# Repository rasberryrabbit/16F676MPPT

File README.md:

# PIC16F676MPPT
Solar MPPT circuit by 16F676. It did tested and work good.

This is simple MPPT for solar panel. PWM driven by software.

11 mili-ohm N-ch logic level FET(BUK9511) used for current sensor. 
It can replace by 11 mili-ohm or higher Rds-on resistance logic level FET.

BUK9511-55A -> BUK9508-55A
Transistor 2N2222A -> BC547 or compatible
Transistor 2N2907A -> BC557 or compatible

L1 100~330uH

LM358N can replace by other pin-compatible regular OP-AMP. HA17358 is good. It has zero offset voltage.

D8-D9 used for 3.6v Reference. Each has about 1.8v voltage drop.

Q1 gate voltage is 3.6v. It's depend on FET specification.

Q1, Q2 can skip heat spreader with low POWER Solar panel. No heat with 10W panel.

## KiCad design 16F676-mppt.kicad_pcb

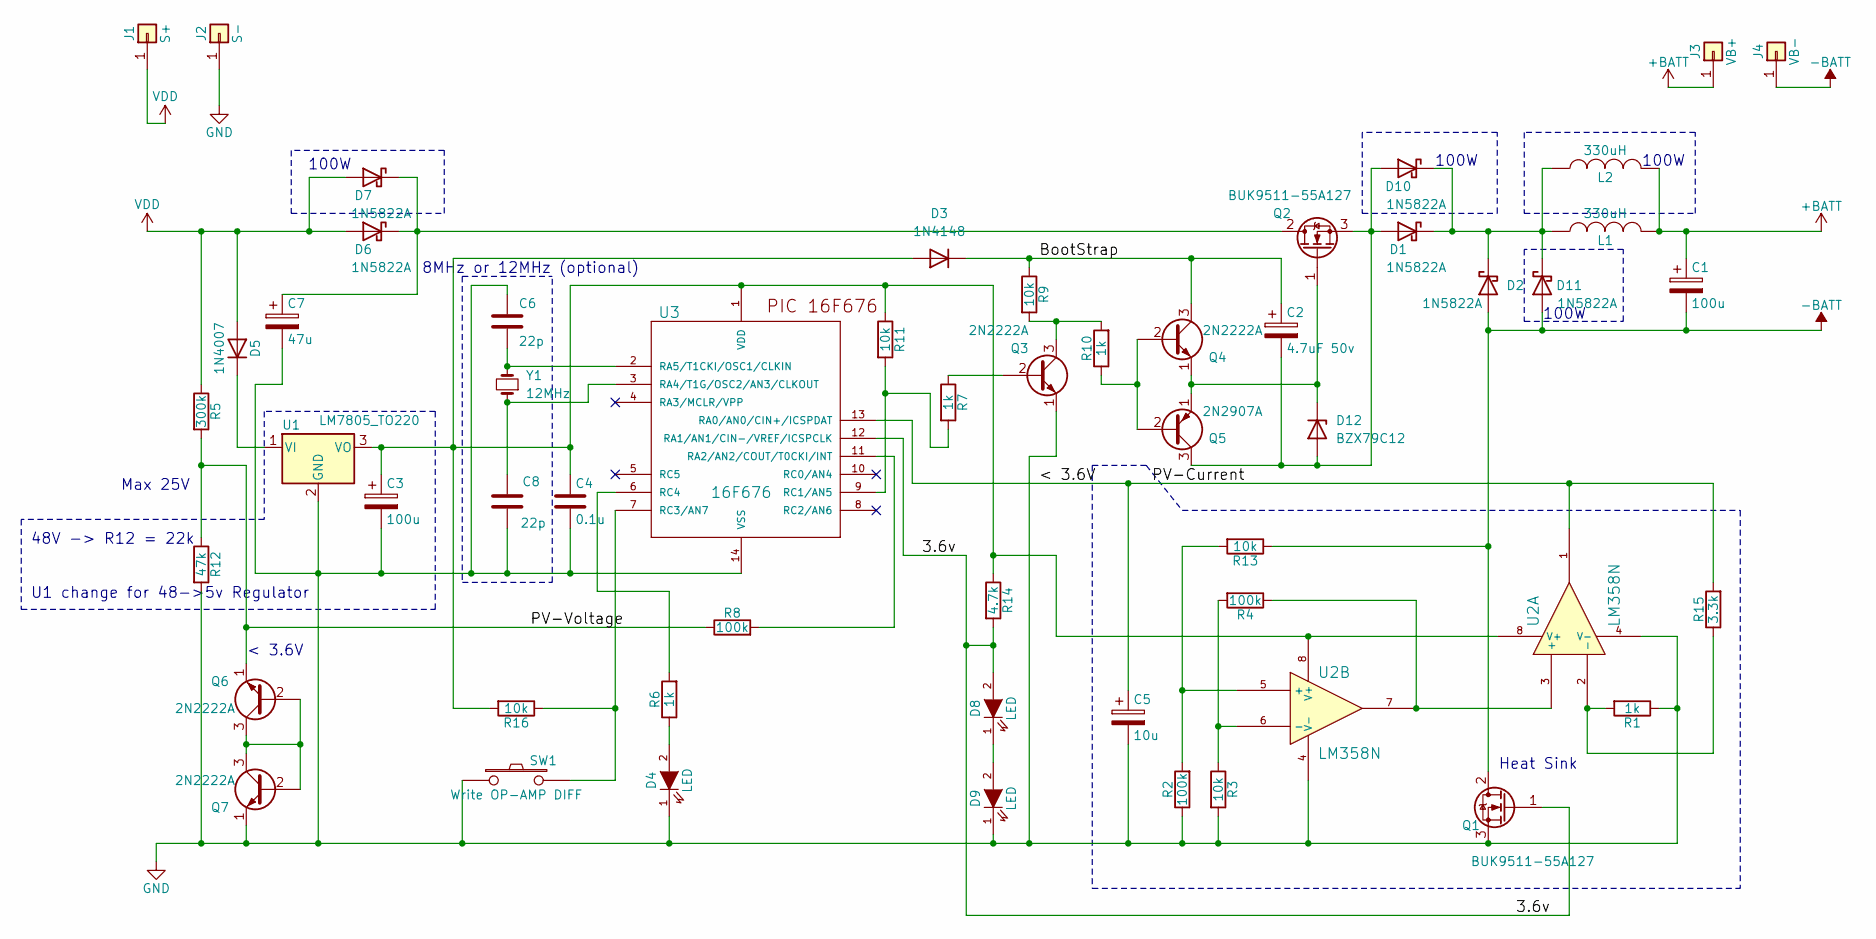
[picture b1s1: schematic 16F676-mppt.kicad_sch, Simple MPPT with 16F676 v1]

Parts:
C1: 100u; CP_Radial_D12.5mm_P5.00mm
C2: 4.7uF 50v; CP_Radial_D8.0mm_P2.50mm
C3: 100u; CP_Radial_D8.0mm_P2.50mm
C4: 0.1u; C_Disc_D12.5mm_W5.0mm_P7.50mm
C5: 10u; CP_Radial_D8.0mm_P2.50mm
C6, C8: 22p; C_Rect_L4.6mm_W2.0mm_P2.50mm_MKS02_FKP02
C7: 47u; CP_Radial_D12.5mm_P5.00mm
D1, D2, D6, D7, D10, D11: 1N5822A; D_DO-201AD_P15.24mm_Horizontal
D3: 1N4148; D_DO-35_SOD27_P7.62mm_Horizontal
D4, D8, D9: LED; LED_D4.0mm
D5: 1N4007; D_DO-41_SOD81_P10.16mm_Horizontal
D12: BZX79C12; D_DO-35_SOD27_P2.54mm_Vertical_AnodeUp
J1: S+; 1pin
J2: S-; 1pin
J3: VB+; 1pin
J4: VB-; 1pin
L1, L2: 330uH; L_Toroid_Vertical_L33.0mm_W17.8mm_P12.70mm_Pulse_KM-5
Q1, Q2: BUK9511-55A127; TO-220-3_Vertical
Q3, Q4, Q6, Q7: 2N2222A; TO-92_Inline_Wide
Q5: 2N2907A; TO-92_Inline_Wide
R1, R6, R7, R10: 1k; R_Axial_DIN0309_L9.0mm_D3.2mm_P12.70mm_Horizontal
R2, R4, R8: 100k; R_Axial_DIN0309_L9.0mm_D3.2mm_P12.70mm_Horizontal
R3, R9, R11, R13, R16: 10k; R_Axial_DIN0309_L9.0mm_D3.2mm_P12.70mm_Horizontal
R5: 300k; R_Axial_DIN0309_L9.0mm_D3.2mm_P12.70mm_Horizontal
R12: 47k; R_Axial_DIN0309_L9.0mm_D3.2mm_P12.70mm_Horizontal
R14: 4.7k; R_Axial_DIN0309_L9.0mm_D3.2mm_P12.70mm_Horizontal
R15: 3.3k; R_Axial_DIN0309_L9.0mm_D3.2mm_P12.70mm_Horizontal
SW1: Write OP-AMP DIFF; SW_PUSH_6mm
U1: LM7805_TO220; TO-220_Vertical
U2: LM358N; DIP-8_W7.62mm
U3: 16F676; DIP-14_W7.62mm
Y1: 12MHz; Crystal_HC49-U_Vertical

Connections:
+BATT: C1.1, J3.1, L1.2, L2.2
-BATT: C1.2, D2.2 (A), D11.2 (A), J4.1, Q1.2 (D), R13.1
/3.6v: D8.2 (A), Q1.1 (G), R14.2, U3.12 (RA1/AN1/CIN-/VREF/ICSPCLK)
/< 3.6V: C5.1, R15.2, U2.1, U3.13 (RA0/AN0/CIN+/ICSPDAT)
/BootStrap: C2.1, D3.1 (K), Q4.3 (C), R9.1
/PV-Voltage: Q6.1 (E), R5.2, R8.1, R12.1
GND: C3.2, C4.2, C5.2, C6.1, C7.2, C8.2, D4.1 (K), D9.1 (K), J2.1, Q1.3 (S), Q3.1 (E), Q7.1 (E), R1.1, R2.1, R3.2, R12.2, SW1.1, U1.2 (GND), U2.4 (V-), U3.14 (VSS)
unnamed: C2.2, D1.2 (A), D10.2 (A), D12.2 (A), Q2.3 (S), Q5.3 (C)
unnamed: D1.1 (K), D2.1 (K), D10.1 (K), D11.1 (K), L1.1, L2.1
unnamed: C3.1, C4.1, D3.2 (A), R11.1, R14.1, R16.2, U1.3 (VO), U2.8 (V+), U3.1 (VDD)
unnamed: D4.2 (A), R6.1
unnamed: D5.1 (K), U1.1 (VI)
unnamed: C7.1, D6.1 (K), D7.1 (K), Q2.2 (D)
unnamed: D8.1 (K), D9.2 (A)
unnamed: D12.1 (K), Q2.1 (G), Q4.1 (E), Q5.1 (E)
unnamed: Q3.2 (B), R7.1
unnamed: Q3.3 (C), R9.2, R10.2
unnamed: Q4.2 (B), Q5.2 (B), R10.1
unnamed: Q6.2 (B), Q6.3 (C), Q7.2 (B), Q7.3 (C)
unnamed: R4.1, U2.3 (+), U2.7
unnamed: R1.2, R15.1, U2.2 (-)
unnamed: R2.2, R13.2, U2.5 (+)
unnamed: R3.1, R4.2, U2.6 (-)
unnamed: R8.2, U3.11 (RA2/AN2/COUT/T0CKI/INT)
unnamed: C8.1, U3.3 (RA4/T1G/OSC2/AN3/CLKOUT), Y1.1
unnamed: C6.2, U3.2 (RA5/T1CKI/OSC1/CLKIN), Y1.2
unnamed: R7.2, R11.2, U3.9 (RC1/AN5)
unnamed: R16.1, SW1.2, U3.7 (RC3/AN7)
unnamed: R6.2, U3.6 (RC4)
VDD: D5.2 (A), D6.2 (A), D7.2 (A), J1.1, R5.1

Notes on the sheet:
8MHz or 12MHz (optional)
U1 change for 48->5v Regulator
100W
Heat Sink
Max 25V
48V -> R12 = 22k
< 3.6V

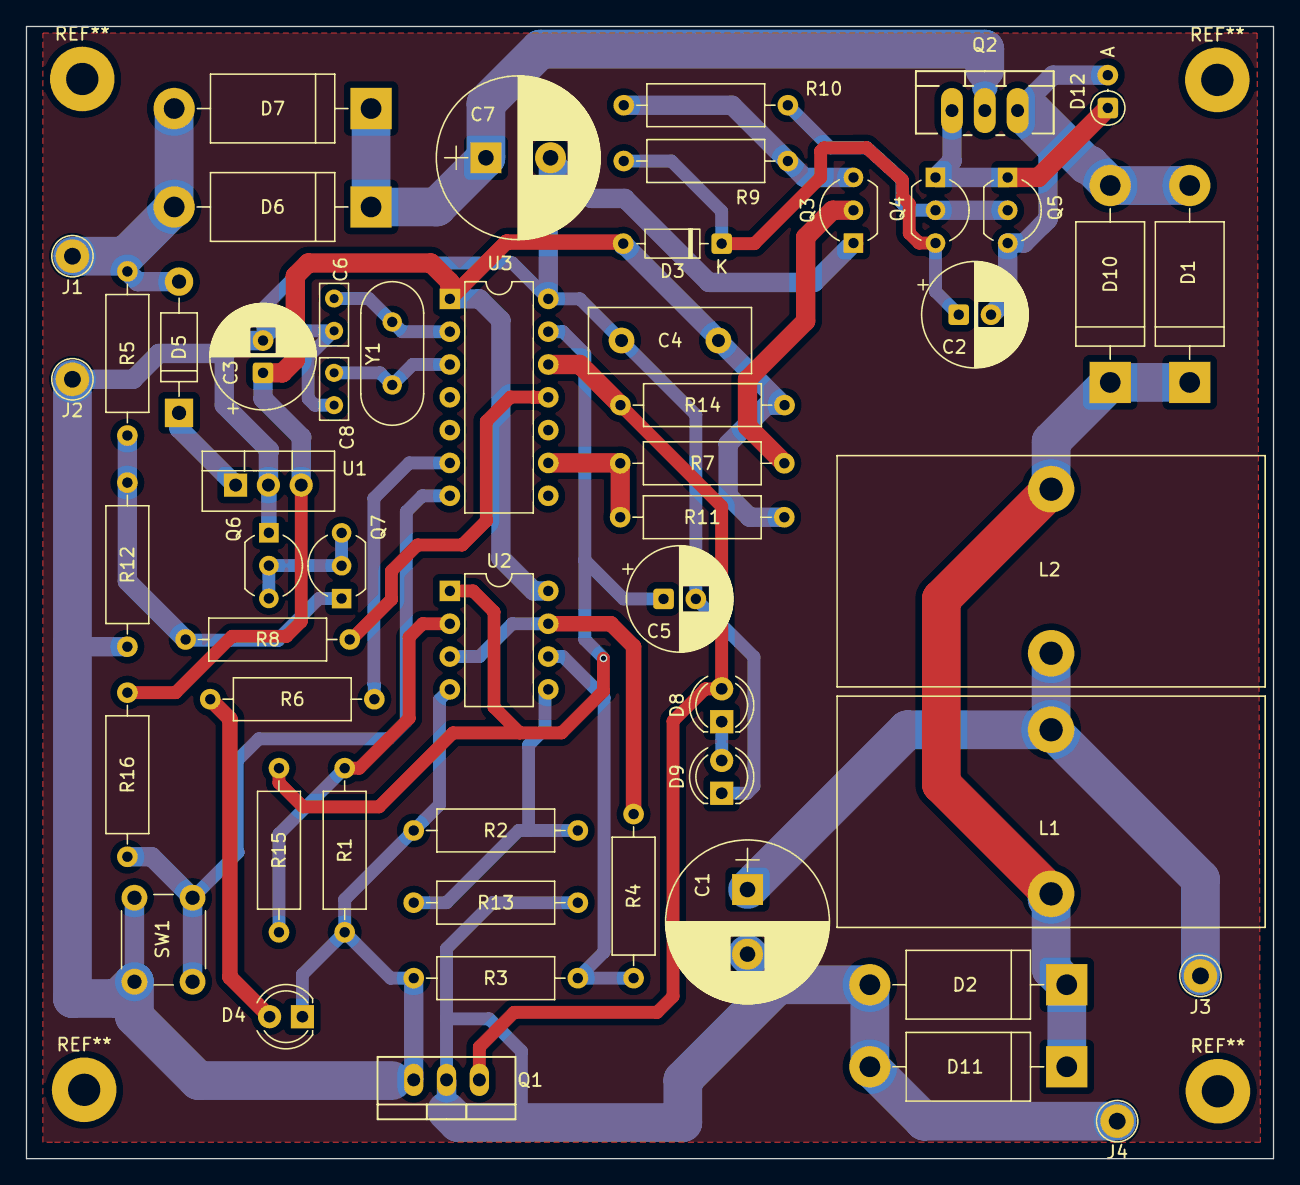
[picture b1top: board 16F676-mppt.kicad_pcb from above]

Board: 2 copper layers, 96.5 x 87.6 mm, 54 parts (0 on the bottom side), 30 nets.

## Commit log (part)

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2018-06-12 first.
2018-06-15 fix missing circuit lines.
2018-06-15 add pcb-layout.
2018-06-30 update pcb.
2018-07-04 change op-amp multiplier resisters.
2018-07-04 update op-amp resister.
2018-07-13 fix silk layer.
2018-07-13 update readme.
2018-07-15 more delay on op-amp calibration.
2018-07-15 make word size
2018-09-04 minor changes.
2018-09-09 Change low PWM limit.
2018-09-10 Decrease low PWM limit for low load stability.
2018-09-11 add parts list.
2018-11-01 Fix FET Bootstrap capacitor.
2018-11-03 More better sustaining PWM.
2018-11-03 Fix low voltage condition. Change method for Max power control.
2018-11-03 fix conditions.
2018-11-03 another condition.
2018-11-04 fix stall at low voltage.
2018-11-13 New method from other project.
2018-11-14 Fix timer function.
2018-11-14 Decrease PWM_MAX to prevent FET switch Bootstrap voltage loss.
2018-11-14 make lower again on PWM_MAX.
2018-11-14 fix PWM_MID.
2018-11-14 Due to software PWM, it cannot sustain high voltage on low light.
2018-11-15 small changes.
2018-11-15 Bootstrap capacitor to 47uF.
2018-11-17 Revert Bootstrap capacitor to 10uF.
2018-11-17 Update but no functional changes.
2018-11-17 Add resistor
2018-11-17 change timer prescaler.
2018-11-17 Add PCB layout.
2018-11-17 Enable brown out detect.
2018-11-17 change bootstrap diode
2018-11-18 update. no functional changes.
2018-11-20 update check delay.
2018-11-27 R11 to 4.7k
2018-11-27 test new firmware.
2018-11-28 update.
2018-11-29 Remove R11, it is a lot lower current sesing voltage.
2018-11-29 Update PCB Layout.
2018-11-29 New ADC read method.
2018-11-30 First working firmware with new method. But it has slow raising time.
2018-11-30 Remove R17.
2018-12-12 increase update interval. change ADC read order.
2018-12-13 fix current ADC reading. update optimized update interval.
2018-12-14 C6 to optinal.
2018-12-15 Remove C6 for better power calculation. I assume low-pass filter but it make negative effect 'low voltage high current stuck'.
2018-12-16 reduce update latency.
2018-12-17 Remove C6.
2018-12-18 Add alternative FET.
2018-12-20 R15 -> 4.7k. Current sensing is more higher than expected. 62mA -> 67mV.
2018-12-22 update R15 value.
2018-12-23 add note for R15.
2018-12-26 add clamp.
2019-01-31 Create LICENSE
2019-02-13 Fix High-z turn on FET problem.
2019-02-15 Change low PWM for boot strap charging.
2019-02-15 Fix R9, R10 Label position.
2019-02-15 Fix R1, R15 values.
2019-02-16 Fix current sensing. I misplace resistors on prototype board.
2019-02-24 Update current sensing resistors.
2019-03-25 Add hint for 48V input.
2019-05-05 Disable sync with PWM clock.
2019-05-06 Enable PWM checking.
2019-06-09 Remove low voltage protection code.
2021-06-30 Set low PWM to 12.
2021-07-11 C2 -> 4.7uF
2021-07-30 Fix Bootstrap problem.
2021-07-30 Revert and change diode.
2021-08-01 Fix power comparison.
2021-08-02 Revert.
2025-12-01 Fix circuit.
2025-12-01 Fix PWM firmware.
2025-12-01 Add optional external xtal.
2025-12-01 Update SCH and PCB files.
